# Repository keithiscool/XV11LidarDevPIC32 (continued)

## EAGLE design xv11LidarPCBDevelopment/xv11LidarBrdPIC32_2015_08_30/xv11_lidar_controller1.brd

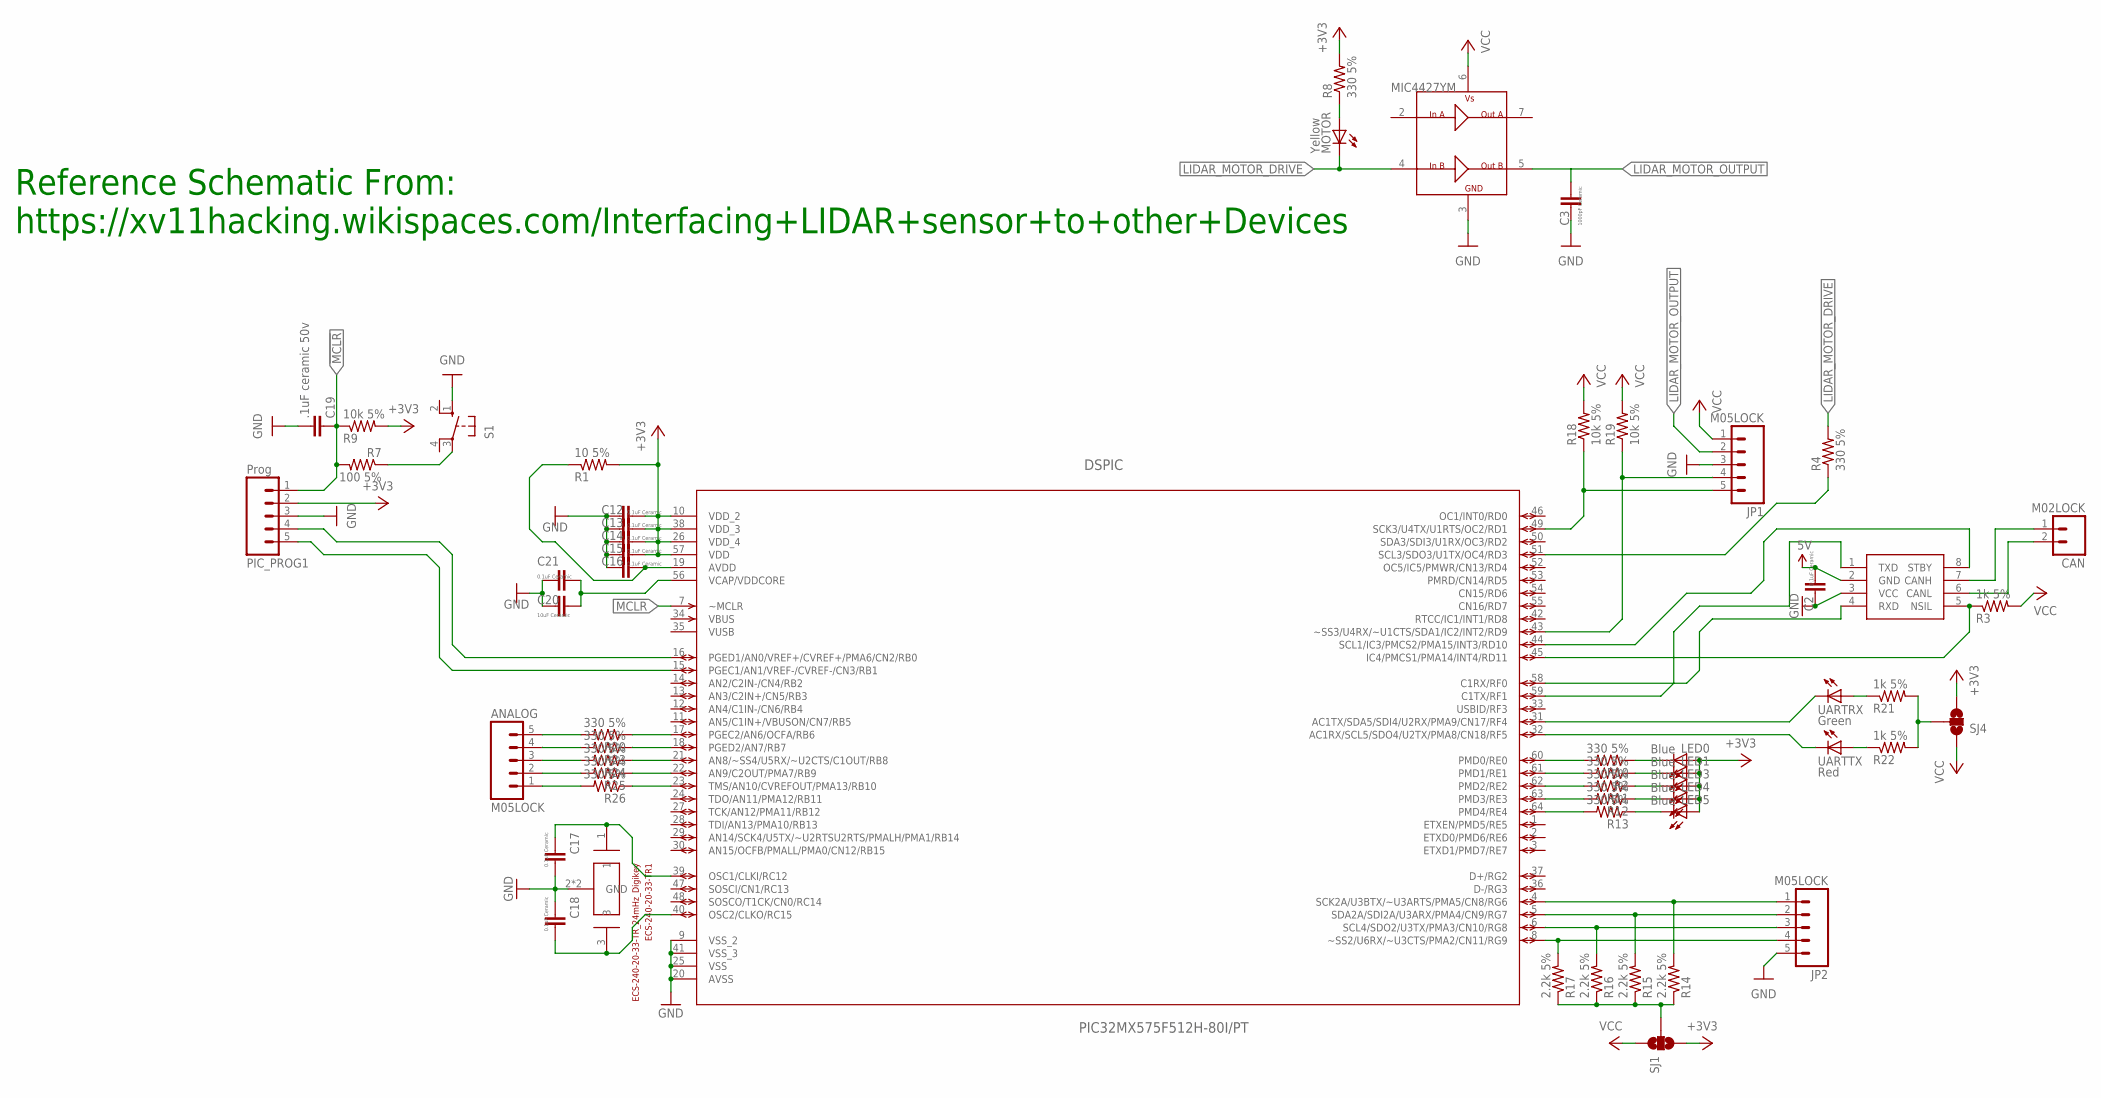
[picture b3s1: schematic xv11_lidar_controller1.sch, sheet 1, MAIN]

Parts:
ANALOG: M05LOCK; 1X05_LOCK
C2, C12, C13, C14, C15, C16, C17, C18, C21: 0.1uF Ceramic; 0805
C3: 1000pF Ceramic; 0805
C19: .1uF ceramic 50v; 0805
C20: 10uF Ceramic; 0805
CAN: M02LOCK; 1X02_LOCK
DSPIC: PIC32MX575F512H-80I/PT; QFP50P1200X1200X120-64N
ECS-240-20-33-TR1: ECS-240-20-33-TR_24mHz_Digikey; ECX-32
JP1, JP2: M05LOCK; 1X05_LOCK
LED0, LED1, LED3, LED4, LED5: Blue; CHIP-LED0805
MOTOR: Yellow; CHIP-LED0805
MOTOR_DRIVER: MIC4427YM; SO-08
PIC_PROG1: Prog; 1X05_LOCK_LONGPADS
R1: 10 5%; R0805
R2, R10, R11, R12, R13, R20, R23, R24, R25, R26: 330 5%; R0805
R3, R21, R22: 1k 5%; M0805
R4, R8: 330 5%; M0805
R7: 100 5%; R0805
R9: 10k 5%; R0805
R14, R15, R16, R17: 2.2k 5%; R0805
R18, R19: 10k 5%; M0805
S1: 10-XX; B3F-10XX
SJ1, SJ4: SOLDERJUMPER_2WAYPASTE1&2; SJ_3_PASTE1&2
U$12: ATA6560; SO08
UARTRX: Green; CHIP-LED0805
UARTTX: Red; CHIP-LED0805

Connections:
5V: C2.2, U$12.2 (GND)
!MCLR: C19.1, DSPIC.7 (~MCLR), PIC_PROG1.1, R7.2, R9.1
+3V3: C12.2, C13.2, C14.2, C15.2, DSPIC.10 (VDD_2), DSPIC.26 (VDD_4), DSPIC.38 (VDD_3), DSPIC.57 (VDD), LED0.A, LED1.A, LED3.A, LED4.A, LED5.A, PIC_PROG1.2, R1.2, R8.2, R9.2, SJ1.3, SJ4.3; also elsewhere on the board
GND: C2.1, C3.1, C12.1, C13.1, C14.1, C15.1, C16.1, C17.2, C18.1, C19.2, C20.1, C21.1, DSPIC.9 (VSS_2), DSPIC.20 (AVSS), DSPIC.25 (VSS), DSPIC.41 (VSS_3), ECS-240-20-33-TR1.2 (GND), ECS-240-20-33-TR1.4 (GND), JP1.3, JP2.5, MOTOR_DRIVER.3 (GND), PIC_PROG1.3, S1.1 (S), U$12.3 (VCC); also elsewhere on the board
LIDAR_MOTOR_DRIVE: MOTOR.C, MOTOR_DRIVER.4 (INB), R4.2
LIDAR_MOTOR_OUTPUT: C3.2, JP1.2, MOTOR_DRIVER.5 (OUTB)
unnamed: DSPIC.4 (SCK2A/U3BTX/~U3ARTS/PMA5/CN8/RG6), JP2.1, R14.2
unnamed: DSPIC.58 (C1RX/RF0), U$12.4 (RXD)
unnamed: DSPIC.59 (C1TX/RF1), U$12.1 (TXD)
unnamed: DSPIC.5 (SDA2A/SDI2A/U3ARX/PMA4/CN9/RG7), JP2.2, R15.2
unnamed: DSPIC.51 (SCL3/SDO3/U1TX/OC4/RD3), R4.1
unnamed: DSPIC.6 (SCL4/SDO2/U3TX/PMA3/CN10/RG8), JP2.3, R16.2
unnamed: DSPIC.8 (~SS2/U6RX/~U3CTS/PMA2/CN11/RG9), JP2.4, R17.2
unnamed: DSPIC.61 (PMD1/RE1), R2.2
unnamed: C17.1, DSPIC.39 (OSC1/CLKI/RC12), ECS-240-20-33-TR1.1
unnamed: C18.2, DSPIC.40 (OSC2/CLKO/RC15), ECS-240-20-33-TR1.3
unnamed: DSPIC.62 (PMD2/RE2), R11.2
unnamed: DSPIC.63 (PMD3/RE3), R12.2
unnamed: DSPIC.64 (PMD4/RE4), R13.2
unnamed: C16.2, DSPIC.19 (AVDD), R1.1
unnamed: C20.2, C21.2, DSPIC.56 (VCAP/VDDCORE)
unnamed: DSPIC.60 (PMD0/RE0), R10.2
unnamed: DSPIC.16 (PGED1/AN0/VREF+/CVREF+/PMA6/CN2/RB0), PIC_PROG1.4
unnamed: LED0.C, R10.1
unnamed: R14.1, R15.1, R16.1, R17.1, SJ1.2
unnamed: LED1.C, R2.1
unnamed: R7.1, S1.3
unnamed: LED3.C, R11.1
unnamed: LED4.C, R12.1
unnamed: LED5.C, R13.1
unnamed: R21.1, UARTRX.A
unnamed: R22.1, UARTTX.A
unnamed: DSPIC.49 (SCK3/U4TX/U1RTS/OC2/RD1), JP1.5, R18.1
unnamed: DSPIC.43 (~SS3/U4RX/~U1CTS/SDA1/IC2/INT2/RD9), JP1.4, R19.1
unnamed: MOTOR.A, R8.1
unnamed: DSPIC.17 (PGEC2/AN6/OCFA/RB6), R20.1
unnamed: DSPIC.18 (PGED2/AN7/RB7), R23.1
unnamed: DSPIC.21 (AN8/~SS4/U5RX/~U2CTS/C1OUT/RB8), R24.1
unnamed: DSPIC.22 (AN9/C2OUT/PMA7/RB9), R25.1
unnamed: DSPIC.23 (TMS/AN10/CVREFOUT/PMA13/RB10), R26.1
unnamed: R21.2, R22.2, SJ4.2
unnamed: ANALOG.5, R20.2
unnamed: ANALOG.4, R23.2
unnamed: ANALOG.3, R24.2
unnamed: ANALOG.2, R25.2
unnamed: ANALOG.1, R26.2
unnamed: CAN.1, U$12.7 (CANH)
unnamed: CAN.2, U$12.6 (CANL)
unnamed: DSPIC.44 (SCL1/IC3/PMCS2/PMA15/INT3/RD10), U$12.8 (STBY)
unnamed: DSPIC.45 (IC4/PMCS1/PMA14/INT4/RD11), R3.1, U$12.5 (NSIL)
PICUART_RX: DSPIC.31 (AC1TX/SDA5/SDI4/U2RX/PMA9/CN17/RF4), UARTRX.C
PICUART_TX: DSPIC.32 (AC1RX/SCL5/SDO4/U2TX/PMA8/CN18/RF5), UARTTX.C
PIC_HANG_CHK: DSPIC.15 (PGEC1/AN1/VREF-/CVREF-/CN3/RB1), PIC_PROG1.5
VCC: JP1.1, MOTOR_DRIVER.6 (VS), R3.2, R18.2, R19.2, SJ1.1, SJ4.1; also elsewhere on the board
VUSB: DSPIC.35 (VUSB)

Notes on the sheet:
Reference Schematic From: https://xv11hacking.wikispaces.com/Interfacing+LIDAR+sensor+to+other+Devices

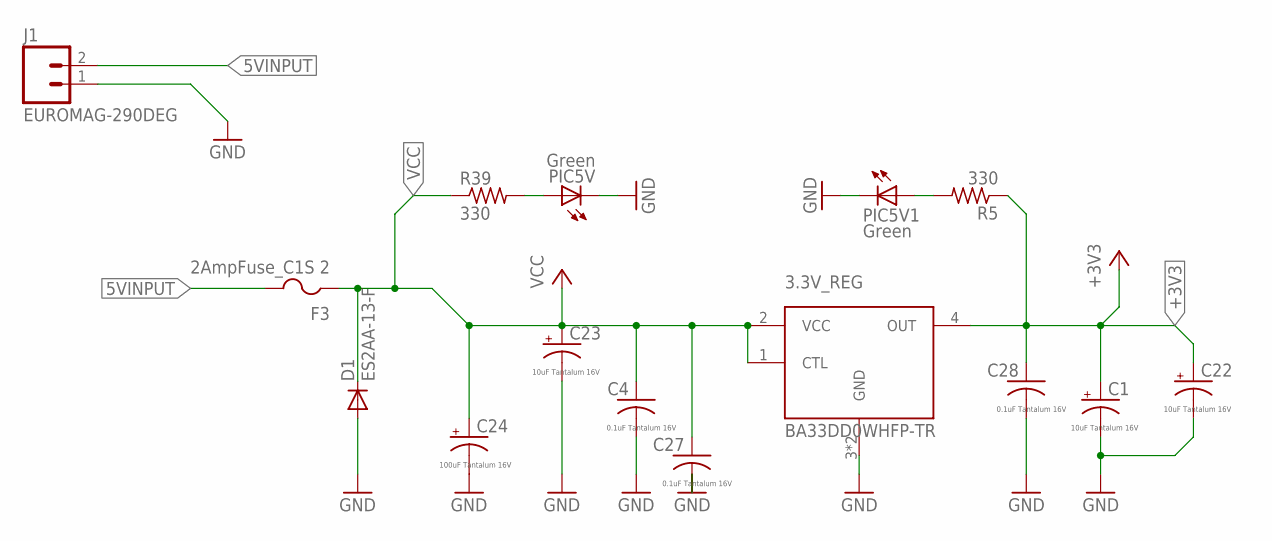
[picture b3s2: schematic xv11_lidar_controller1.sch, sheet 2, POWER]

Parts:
3.3V_REG: BA33DD0WHFP-TR; HRP5
C1, C22, C23: 10uF Tantalum 16V; EIA3216
C4, C27, C28: 0.1uF Tantalum 16V; C0805K
C24: 100uF Tantalum 16V; EIA3216
D1: ES2AA-13-F; SMA-DIODE
F3: 2AmpFuse_C1S 2; R1206
J1: EUROMAG-290DEG; M2
PIC5V, PIC5V1: Green; CHIP-LED0805
R5, R39: 330; R0805

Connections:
5VINPUT: F3.2, J1.2
+3V3: 3.3V_REG.4 (OUT), C1.A (+), C22.A (+), C28.1, R5.1; also elsewhere on the board
GND: 3.3V_REG.3 (GND), 3.3V_REG.G (GND), C1.C (-), C4.2, C22.C (-), C23.C (-), C24.C (-), C27.2, C28.2, D1.A, J1.1, PIC5V.C, PIC5V1.C; also elsewhere on the board
unnamed: PIC5V1.A, R5.2
unnamed: PIC5V.A, R39.2
VCC: 3.3V_REG.1 (CTL), 3.3V_REG.2 (VCC), C4.1, C23.A (+), C24.A (+), C27.1, D1.C, F3.1, R39.1; also elsewhere on the board

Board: 2 copper layers, 71 parts (0 on the bottom side), 57 nets, no tracks yet.

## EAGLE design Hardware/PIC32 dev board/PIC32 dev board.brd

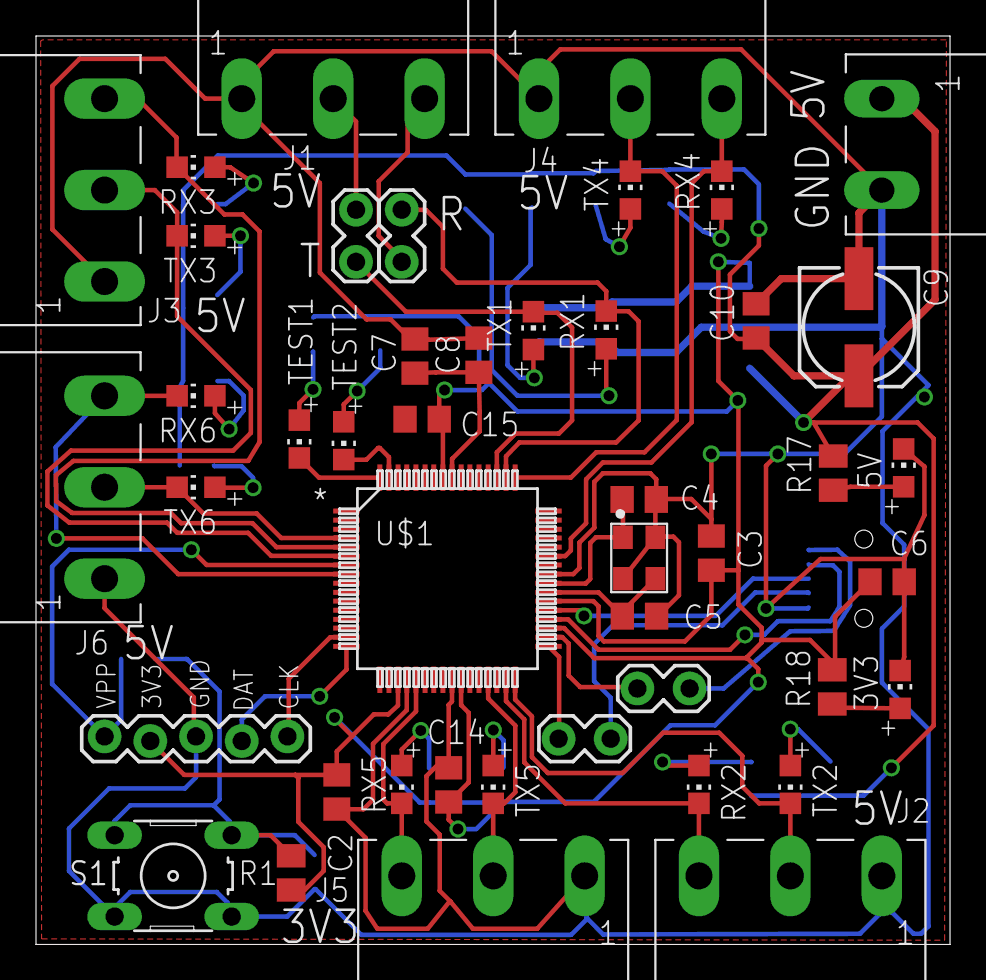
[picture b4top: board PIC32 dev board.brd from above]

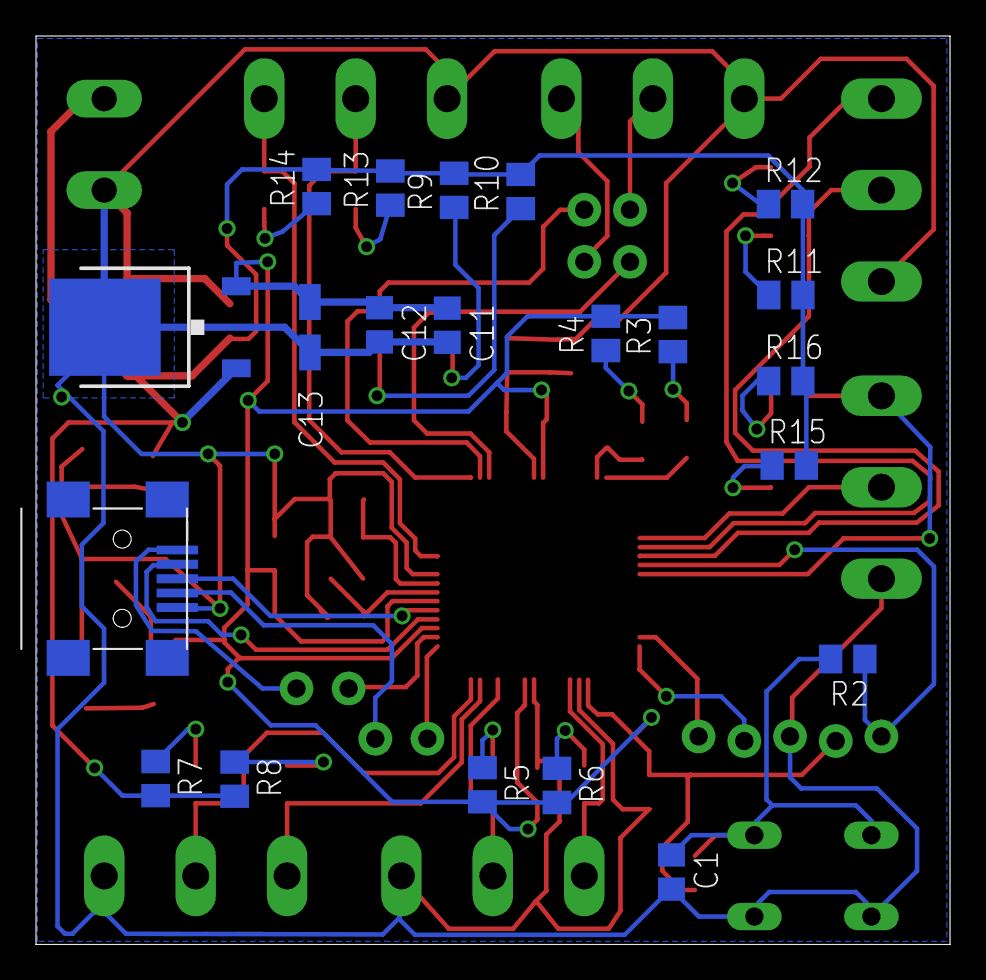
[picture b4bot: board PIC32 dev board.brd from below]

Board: 2 copper layers, 50.8 x 50.5 mm, 66 parts (21 on the bottom side), 48 nets.

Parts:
3V3, 5V: Green; CHIP-LED0805
C1, C2, C3, C6, C7, C10, C11, C14, C15: 0.1 uF ceramic 50v; C0805
C4, C5: 30 pF ceramic 50v; C0805
C8: optional 10 uF ceramic 50v; C0805
C9: 100 uF aluminum 16v; 153CLV-0605
C12: optional 0.1 uF ceramic 50v; C0805
C13: 10uF tantilum 16v; CT3216
CN1: USB-MINIB
ECS-240-20-33-TR: CRYSTAL; ECX-32
J1, J2, J3, J4, J5, J6: EUROMAG-390DEG; M3
J7: EUROMAG-290DEG; M2
JP1: 1X05_LOCK
JP2, JP3, JP4, JP5: M02LOCK; 1X02_LOCK
R1: 10K; M0805
R2: 499R; M0805
R3, R4: 330R; M0805
R5, R6, R18: 665R; M0805
R7, R8, R9, R10, R11, R12, R13, R14, R15, R16, R17: 1K; M0805
RX1, RX2, RX3, RX4, RX5, RX6: Green; CHIP-LED0805
S1: B3F-10XX
TEST1, TEST2: Blue; CHIP-LED0805
TX1, TX2, TX3, TX4, TX5, TX6: Red; CHIP-LED0805
U$1: PIC32MX575F512H-X_PT; TQFP64_10X10MC
U$2: LP2950; TO-252

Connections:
+3V3: C2.1, C3.1, C6.1, C11.1, C12.1, C13.+, C14.1, C15.1, JP1.2, R1.2, R3.2, R4.2, R5.2, R6.2, R18.2, U$1.19, U$1.26, U$1.35, U$1.38, U$1.57, U$2.OUTPUT
+5V: C9.+, C10.1, J7.1, R7.2, R8.2, R9.2, R10.2, R11.2, R12.2, R13.2, R14.2, R15.2, R16.2, R17.2, U$2.INPUT
GND: 3V3.C, 5V.C, C1.2, C2.2, C3.2, C4.2, C5.2, C6.2, C7.2, C8.2, C9.-, C10.2, C11.2, C12.2, C13.-, C14.2, C15.2, CN1.GND, ECS-240-20-33-TR.2, ECS-240-20-33-TR.4, J1.1, J2.1, J3.1, J4.1, J5.1, J6.1, J7.2, JP1.3, S1.3, S1.4, U$1.20, U$1.25, U$1.41, U$2.GROUND
unnamed: J5.2, TX5.C, U$1.29
unnamed: J5.3, RX5.C, U$1.21
unnamed: J1.2, JP4.1
unnamed: J1.3, JP3.1
unnamed: J4.2, TX4.C, U$1.49
unnamed: JP3.2, RX1.C, U$1.50
unnamed: J2.2, TX2.C, U$1.32
unnamed: J2.3, RX2.C, U$1.31
unnamed: J3.2, TX3.C, U$1.6
unnamed: J3.3, RX3.C, U$1.5
unnamed: J6.2, TX6.C, U$1.4
unnamed: J6.3, RX6.C, U$1.8
unnamed: JP1.1, R2.1, U$1.7
unnamed: JP1.4, U$1.16
unnamed: JP1.5, U$1.15
unnamed: C1.1, R1.1, R2.2, S1.1, S1.2
unnamed: C7.1, C8.1, U$1.56
unnamed: C4.1, ECS-240-20-33-TR.1, U$1.40
unnamed: C5.1, ECS-240-20-33-TR.3, U$1.39
unnamed: CN1.D+, U$1.37
unnamed: CN1.D-, U$1.36
unnamed: CN1.VBUS, JP5.1
unnamed: CN1.ID, JP2.1
unnamed: TEST2.C, U$1.63
unnamed: TEST1.C, U$1.64
unnamed: R3.1, TEST1.A
unnamed: R4.1, TEST2.A
unnamed: R5.1, TX5.A
unnamed: R6.1, RX5.A
unnamed: R7.1, TX2.A
unnamed: R8.1, RX2.A
unnamed: R9.1, TX1.A
unnamed: R10.1, RX1.A
unnamed: R11.1, TX3.A
unnamed: R12.1, RX3.A
unnamed: R13.1, TX4.A
unnamed: R14.1, RX4.A
unnamed: R15.1, TX6.A
unnamed: R16.1, RX6.A
unnamed: JP2.2, U$1.33
unnamed: JP4.2, TX1.C, U$1.51
unnamed: J4.3, RX4.C, U$1.43
unnamed: JP5.2, U$1.34
unnamed: 5V.A, R17.1
unnamed: 3V3.A, R18.1

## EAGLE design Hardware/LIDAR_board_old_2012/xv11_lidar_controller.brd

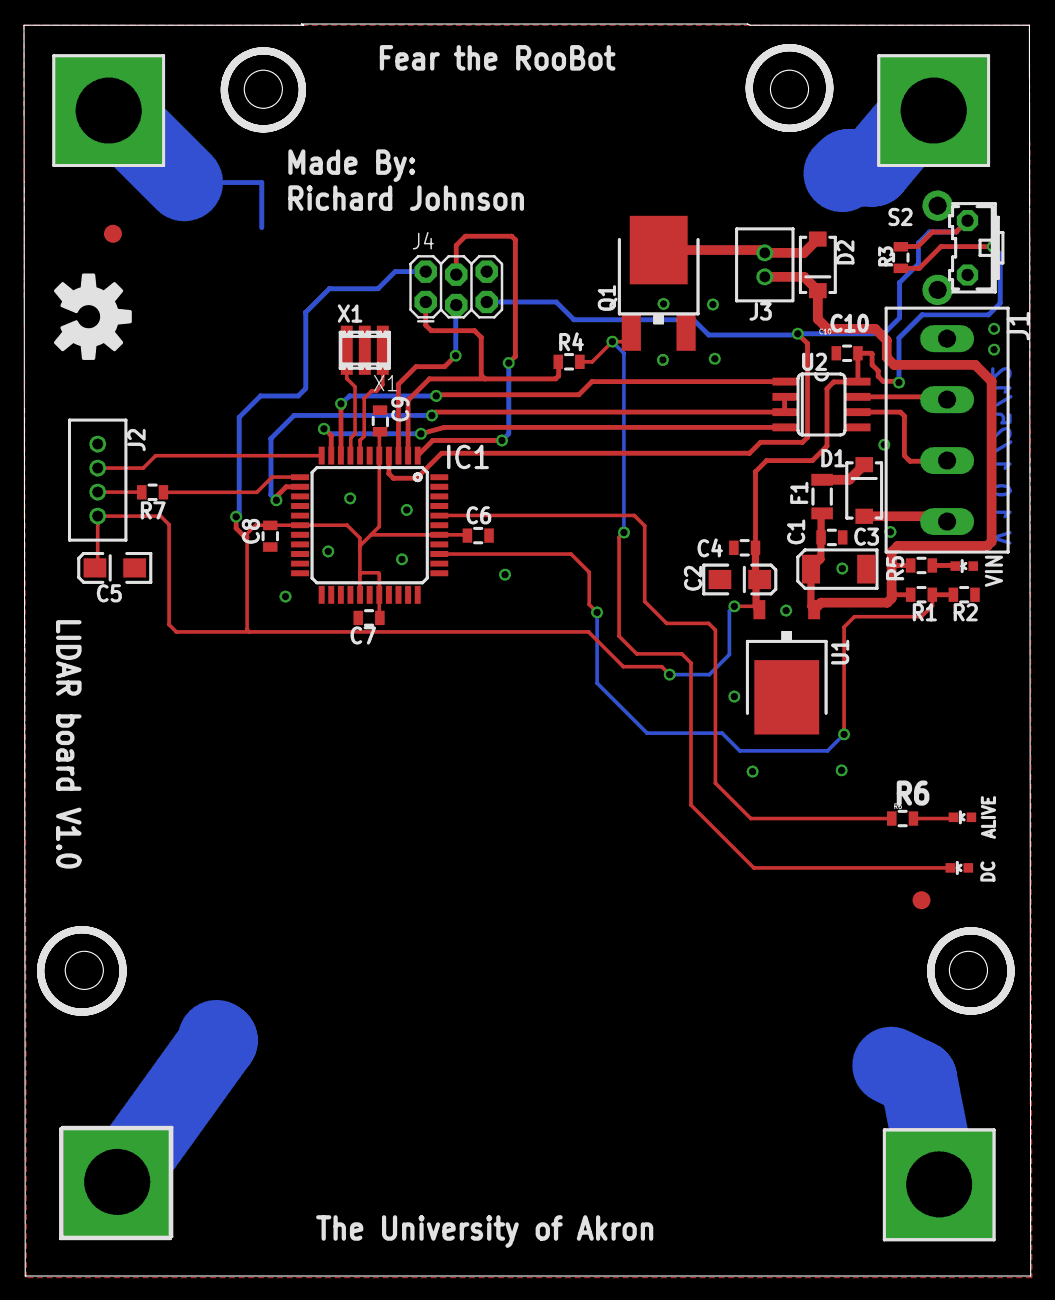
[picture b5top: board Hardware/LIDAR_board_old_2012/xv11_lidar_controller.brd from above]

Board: 2 copper layers, 83.9 x 104.3 mm, 40 parts (0 on the bottom side), 25 nets.

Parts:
C1: 10uF; EIA6032
C2, C5: 10uF; EIA3216-KIT
C3, C4, C6, C7, C8, C9, C10: .1uF; 0805
D1, D2: SMA-DIODE
F1: PTCSMD; PTC-1206
H1, H2, H3, H4: 5,5-PAD-SQUARE
IC1: ATMEGA644A; TQFP44
J1: EUROMAG-4; M4
J2: LIDAR4POS; 2MM4POS
J3: LIDAR2POS; 2MM2POS
J4: AVR_SPI_PRG_62X3_LOCK; 2X3_LOCK
JP1, JP2: FIDUCIAL1.5X3; FIDUCIAL-1.5X3
LED1: VIN; LED-0603
LED2: ALIVE; LED-0603
LED3: DC; LED-0603
Q1: MOSFET-NCHANNELFDD8580; DPAK
R1, R2: 0805
R3: 10k; 0805
R4, R5, R6, R7: 1k; 0805
S2: B3F-31XX
U1: 7805DT; TO252
U2: MAX485SO; SO08
U$2: OSHW-LOGOL; OSHW-LOGO-L
X1: AWCSR

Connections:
5V: C2.A, C4.1, C5.A, C6.1, C7.1, C8.1, C9.1, C10.1, IC1.5, IC1.17, IC1.27, IC1.29, IC1.38, J2.1, J4.2, R3.2, U1.2, U2.8
ADCVIN: IC1.36, R1.1, R2.2
GND: C1.P$2, C2.C, C3.2, C4.2, C5.C, C6.2, C7.2, C8.2, C9.2, C10.2, H1.B5,5, H2.B5,5, H3.B5,5, H4.B5,5, IC1.6, IC1.18, IC1.28, IC1.39, J1.P$1, J2.4, J4.6, LED1.A, LED2.A, LED3.A, Q1.3, R2.1, S2.1, U1.3, U2.5, X1.2
LRX: J2.2, R7.2
LTX: IC1.11, J2.3
MISO: IC1.2, J4.1, R4.2
MOSI: IC1.1, J4.4
unnamed: D1.A, J1.P$4
unnamed: D1.C, F1.1
unnamed: LED3.C, Q1.1, R4.1
unnamed: LED1.C, R5.1
unnamed: IC1.40, R6.1
unnamed: LED2.C, R6.2
unnamed: D2.A, J3.P$2, Q1.4
unnamed: IC1.13, U2.2, U2.3
unnamed: IC1.12, R7.1
unnamed: IC1.7, X1.1
unnamed: IC1.8, X1.3
RS485+: J1.P$3, U2.6
RS485-: J1.P$2, U2.7
RST: IC1.4, J4.5, R3.1, S2.2
RXD: IC1.9, U2.1
SCK: IC1.3, J4.3
TXD: IC1.10, U2.4
VIN: C1.P$1, C3.1, D2.C, F1.2, J3.P$1, R1.2, R5.2, U1.1

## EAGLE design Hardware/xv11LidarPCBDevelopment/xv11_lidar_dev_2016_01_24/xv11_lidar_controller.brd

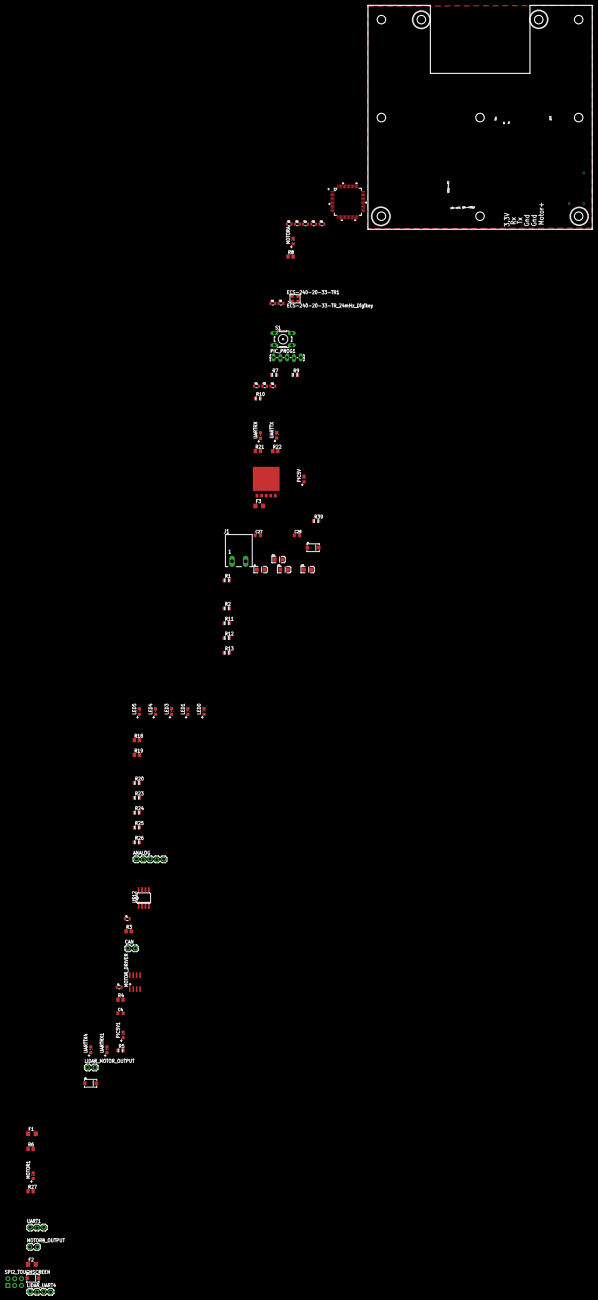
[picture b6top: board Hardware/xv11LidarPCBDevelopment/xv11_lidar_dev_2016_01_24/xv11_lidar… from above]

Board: 2 copper layers, 83.8 x 83.6 mm, 77 parts (0 on the bottom side), 64 nets, no tracks yet.

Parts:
3.3V_REG: BA33DD0WHFP-TR; HRP5
ANALOG: M05LOCK; 1X05_LOCK
C1, C22, C23: 10uF Tantalum 16V; EIA3216
C2: 0.1uF Ceramic 50v; 0805
C3: 1000pF Ceramic 50V; 0805
C4, C27, C28: 0.1uF Tantalum 16V; C0805K
C12, C13, C14, C15, C16, C17, C18, C21: 0.1uF Ceramic; 0805
C19: .1uF ceramic 50v; 0805
C20: 10uF Ceramic; 0805
C24: 100uF Tantalum 16V; EIA3216
CAN: M02LOCK; 1X02_LOCK
D1, D2, D3: ES2AA-13-F; SMA-DIODE
ECS-240-20-33-TR1: ECS-240-20-33-TR_24mHz_Digikey; ECX-32
F1, F2: 1AmpFuse_C1S 2; R1206
F3: 2AmpFuse_C1S 2; R1206
J1: EUROMAG-290DEG; M2
LED0, LED1, LED3, LED4, LED5: Blue; CHIP-LED0805
LIDAR_MOTOR_OUTPUT: M02LOCK; 1X02_LOCK
LIDAR_UART4: 1X04_LOCK
MOTOR1: Yellow; CHIP-LED0805
MOTORA: Yellow; CHIP-LED0805
MOTORB_OUTPUT: M02LOCK; 1X02_LOCK
MOTOR_DRIVER: MIC4427YM; SO-08
PIC5V, PIC5V1: Green; CHIP-LED0805
PIC32: PIC32MX575F512H-80I/PT; QFP50P1200X1200X120-64N
PIC_PROG1: Prog; 1X05_LOCK_LONGPADS
R1: 10 5%; R0805
R2, R10, R11, R12, R13: 330 5%; R0805
R3: 1k 5%; M0805
R4, R6: 100 5%; M0805
R5, R39: 330; R0805
R7, R20, R23, R24, R25, R26: 100 5%; R0805
R8, R27: 330 5%; M0805
R9: 10k 5%; R0805
R18, R19, R21, R22: 2.2k 5%; M0805
S1: B3F-10XX
SPI2_TOUCHSCREEN: 2X3-NS
U$12: ATA6560; SO08
UART1: M03LOCK; 1X03_LOCK
UARTRX, UARTRX1: Green; CHIP-LED0805
UARTTX, UARTTX4: Red; CHIP-LED0805

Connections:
5V: C2.2, U$12.2
5VINPUT: F3.2, J1.2
!MCLR: C19.1, PIC32.7, PIC_PROG1.1, R7.2, R9.1
+3V3: 3.3V_REG.4, C1.A, C12.2, C13.2, C14.2, C15.2, C22.A, C28.1, LED0.A, LED1.A, LED3.A, LED4.A, LED5.A, PIC32.10, PIC32.26, PIC32.38, PIC32.57, PIC_PROG1.2, R1.2, R5.1, R8.2, R9.2, R21.2, R22.2, R27.2
GND: 3.3V_REG.3, 3.3V_REG.G, C1.C, C2.1, C3.1, C4.2, C12.1, C13.1, C14.1, C15.1, C16.1, C17.2, C18.1, C19.2, C20.1, C21.1, C22.C, C23.C, C24.C, C27.2, C28.2, D1.A, D2.A, D3.A, ECS-240-20-33-TR1.2, ECS-240-20-33-TR1.4, J1.1, LIDAR_MOTOR_OUTPUT.2, LIDAR_UART4.4, MOTORB_OUTPUT.2, MOTOR_DRIVER.3, PIC5V.C, PIC5V1.C, PIC32.9, PIC32.20, PIC32.25, PIC32.41, PIC_PROG1.3, S1.1, SPI2_TOUCHSCREEN.6, U$12.3, UART1.3
LIDAR_MOTOR_DRIVE: MOTORA.C, MOTOR_DRIVER.4
LIDAR_MOTOR_OUTPUT: D2.C, F1.1, LIDAR_MOTOR_OUTPUT.1
LIDAR_MOTOR_OUTPUT1: D3.C, F2.1, MOTORB_OUTPUT.1
MOTORB_DRIVE: MOTOR1.C, MOTOR_DRIVER.2, R6.2
unnamed: R18.2, R19.2
unnamed: PIC32.58, U$12.4
unnamed: PIC32.59, U$12.1
unnamed: C3.2, F1.2, MOTOR_DRIVER.5
unnamed: PIC32.51, R4.1
unnamed: PIC32.50, R6.1
unnamed: PIC5V1.A, R5.2
unnamed: R18.1, UARTRX1.A
unnamed: MOTOR1.A, R27.1
unnamed: PIC32.61, R2.2
unnamed: C17.1, ECS-240-20-33-TR1.1, PIC32.39
unnamed: C18.2, ECS-240-20-33-TR1.3, PIC32.40
unnamed: PIC32.62, R11.2
unnamed: PIC32.63, R12.2
unnamed: PIC32.64, R13.2
unnamed: C16.2, PIC32.19, R1.1
unnamed: C20.2, C21.2, PIC32.56
unnamed: PIC32.60, R10.2
unnamed: PIC32.16, PIC_PROG1.4
unnamed: LED0.C, R10.1
unnamed: PIC32.8, SPI2_TOUCHSCREEN.4
unnamed: LED1.C, R2.1
unnamed: R7.1, S1.3
unnamed: LED3.C, R11.1
unnamed: LED4.C, R12.1
unnamed: LED5.C, R13.1
unnamed: R21.1, UARTRX.A
unnamed: R22.1, UARTTX.A
unnamed: LIDAR_UART4.3, PIC32.49, UARTRX1.C
unnamed: LIDAR_UART4.2, PIC32.43, UARTTX4.C
unnamed: MOTORA.A, R8.1
unnamed: PIC32.17, R20.1
unnamed: PIC32.18, R23.1
unnamed: PIC32.21, R24.1
unnamed: PIC32.22, R25.1
unnamed: PIC32.23, R26.1
unnamed: ANALOG.5, R20.2
unnamed: ANALOG.4, R23.2
unnamed: ANALOG.3, R24.2
unnamed: ANALOG.2, R25.2
unnamed: ANALOG.1, R26.2
unnamed: R19.1, UARTTX4.A
unnamed: CAN.1, U$12.7
unnamed: CAN.2, U$12.6
unnamed: PIC32.44, U$12.8
unnamed: PIC32.45, R3.1, U$12.5
unnamed: F2.2, MOTOR_DRIVER.7
unnamed: PIC5V.A, R39.2
PICUART_RX: PIC32.31, UART1.1, UARTRX.C
PICUART_TX: PIC32.32, UART1.2, UARTTX.C
PIC_HANG_CHK: PIC32.15, PIC_PROG1.5
SCK2: PIC32.4, SPI2_TOUCHSCREEN.1
SDI2: PIC32.5, SPI2_TOUCHSCREEN.3
SDO2: PIC32.6, SPI2_TOUCHSCREEN.5
VCC: 3.3V_REG.1, 3.3V_REG.2, C4.1, C23.A, C24.A, C27.1, D1.C, F3.1, LIDAR_UART4.1, MOTOR_DRIVER.6, R3.2, R39.1, SPI2_TOUCHSCREEN.2

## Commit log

2016-01-31 :lollipop: Added .gitattributes
2016-01-31 First Commit
    Checksum rejecting not letting data populate Distance[360] array
2016-02-01 Active Polar Readout Added
    Added Faster Printout over UART (Putchar function delay reduced for U1TX
    debugging to PC)
    Hope to test cartesian distances and test for real
    NEED TO MAKE PRINTOUT REFRESH FASTER!!!
2016-02-05 NOT_WORKING_ALMOST_WORKING
    Backup_2016_02_04
2016-02-13 BrokenNewCopy_2016_02_12_Friday
    BrokenUARTVersion(Friday2016_02_12)
2016-02-13 SuccessfulWorkingCopy
    Works quickly (populates polar data in 40 seconds), but using delayed
    putchar() function in uart_handler.c
    **FOR FUTURE: NEED TO USE INTERRUPTS WITH THE UART U1TX
    NOW WORKS WITH 230400 BAUDRATE FOR U1TX TO TERMINAL
2016-03-19 NOT_WORKING_2016_03_19
    Starting to Add DMA stuff
2016-03-19 NOT_WORKING_1230pm
2016-03-20 TestCodeForTomorrow
    Actually started the DMA (I did not call it in initialize.c before now
    from initialize function)
2016-03-20 Working DMA!!!!
    Need to format the data to show up in terminal better
2016-03-23 Trying to get DMA to print out data better
    data only prints 1 row and repeats (probably something with the DMA
    layers
2016-04-16 adding more object detection calculations
2016-04-17 NEW_BOARD_NOT_WORKING
    LidarIn: from U5RX to U4RX
    DebugOut: from U1TX to U6TX
2016-04-17 PROJECT_NOT_WORKING_cleaned up folder
2016-04-30 WorkingCodeNEW_BOARD
    need to fix dma output
2016-04-30 DMA_Troubleshooting_NotAllDataBeingSent
2016-04-30 MinorChanges_DMAstillNotCorrectOutput
2016-05-05 DMA almost working_extra zeros between data elements
    blah
2016-05-06 almost_working_too_many_zeros
2016-05-06 data invalid shows as "7777"
2016-05-08 Motor Speed and Quality Checks for Data
    Quality Check array added to check reflectance of light coming back from
    objects.
    DEBUG THE QUALITY COMING BACK
    Also - changed motor speed to 230RPM
2016-05-08 Working Modular Code
    Not the user can decide if the parsed data should be printed or not.
2016-05-13 NOT_WORKING_CODE
    Added object detection logic
    indexed lidar offset by 90 degrees
    trying to use blinking LEDs and timers for dubugging
2016-05-14 NOT_Working_ObjectDectectionUpdated
2016-05-14 Debug_Code_ok
    need to test without printing data out
2016-05-14 troubleshooting timers and object detection
2016-05-14 object_detection_using_struct_array
    object detection with struct
    cleaned up folder with excess stuff
2016-05-14 timer_works
2016-05-15 fixed timer issue_working_in_debug_mode
2016-05-15 WORKING_CODE_MustTestObjectDetectionForAccuracy
    Changed DMA times
    added debugging to showobjects
    **not checking for objects that are close to each other (commented out
    the checking of duplicate objects close to each other)**
2016-05-16 TroubleshootingOffestOfLidar_DegreeIndex_Not_Correct
2016-05-16 object_detection_ok_in_sun
2016-05-16 ERROR_Return_False_Line122_lidar_decoder.c
    Do not know why rejecting the angles behind the lidar prevents objects
    from being detected...
2016-05-16 current_working
2016-05-17 fixes
2016-05-17 troubleshooting
    counter fix
    array length fix
2016-05-19 RebuildingCode_NotUsingDMA_UARTonly
    must send object information to host
2016-05-19 WorkingDebugCode_ObjectTrackingStarting
2016-05-19 ADDED_AWESOME_BLINKING_LEDS
2016-05-19 Untested_FixingFixedPointMath
    signed vs unsigned
2016-05-19 added some debugging for testing the cartesian calculation
2016-05-19 CartesianIsNotCorrect_FIXINGlookupTable
2016-05-19 NOT_WORKING_FixingTrigLookupTable
2016-05-19 Fixing Sin Lookup Table2
2016-05-19 Debug_Data_withFixedCartesianFixedPoint
2016-05-19 FixingFixedPoint
2016-05-19 not working fixed point
2016-05-19 BAD_LookupTableCartesian
2016-05-19 startingObjectDetection
2016-05-20 ObjectDetectionVERY_CLOSE
2016-05-20 debug_need to filter degree zero
2016-05-20 Working_YESSSS
2016-05-20 WORKING_CODE_DetectionOfObjects
    Need to filter objects
    1) prevent duplicate objects from future detections
    2) possibly track moving objects
2016-05-20 Added_WiiCam_Stuff
2016-06-03 UNTESTED_AddedSimpleRollingAverageAndCleanedUpCode
2016-06-04 WORKING_ObjectTracking
    Added sendRobotLocation() function
    this will be used to send info to navigation processor on the robot.
    **Need to print objects out using a timer to debug the project easier**
2016-06-04 ForgotAFile?? ObjectDetect.c???
2016-06-04 ADDED DOCUMENTATION
    AddedPictureOfDataRecordedForObject
    Corrected FloatingPointMath in Object Detection
2016-06-04 CleaningUpCode
    Commented out Trig Fixed Point Lookup Table to save memory
2016-06-04 Fixed degrees->radians conversion - NEED TO FIX X-OFFSET OF BEACON (NOT IN CENETER OF ARENA
    Beacon is not in ceneter of arena, so X_POSITION_OFFSET_LIDAR_PLACEMENT
    needs to be tuned and DetectedObject.xPos needs to be tuned in testing
2016-06-08 UNTESTED_VeclocityVectorAndBearingTrackingOfRobotWhileRobotMoves
    Velocity calculation
    Compass directections (general directed approximation added -->
    North,South,East,West,NE,NW,SE,SW)
    using quality to check how reflective the robot is -->
    if(quality>thresh), found robot!!!!!!!
    Arena perimeter limits were added after looking at included
2016-06-09 VelocityAndBearingRobotObjectCalcsAreIncorrect
    *Need to fix velocity calculations
    1)Tuned quality of object that it must be within to count as object
    2)Added Law of Cosines to calculate the diameter of the object
    3) object must have moved "objectMovedThreshold" in either the x or y
    direction since the last reading
2016-06-09 fixed error with vector math (units were not reflected in math
2016-06-11 Fixed Bearing and Velocity calculations in Objectracking.c
    Velocity was changed to subtract last and present x,y terms
    Also bearing calculation was converted from radians to degrees.
2016-06-11 DistDiffArr Fixes for finding starting edge and stopping edge
    Fixed DistDiffArr --> it was declared unsigned
    Fixed how I solved for the DistDiffArr values --> was taking absolute
    val
2016-06-12 NOT_Working_AttemptingToFixPositiveandNegativeEdgeDetection
    Fixed DistanceDiffArr was unsigned (needs to be signed for subtraction
    DistanceDiff should not be using absolute value
    **Positive/leading edge of object should have positive value and
    negative/trailing edge should have negative value**
2016-06-18 Added Readme.md file for documentation
